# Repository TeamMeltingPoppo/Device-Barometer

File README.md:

# Device-Template

> A template for building applications for Twelite

This project is developed and maintained by the Team NABA

## Dependencies

To build embedded programs using this template you'll need:

- KiCad Version: 8.0.0, or a newer version.

- Git client

- Github CLI (optional)

## Usage

1. Repositoryを作成するときに、Repository Templateとして`TeamMeltingPoppo/Device-Template`を選択してください。

2. Repository名は、`Device-`から始まる名前にしてください。

3. 作成したRepositoryに移動し、`setup.sh`を実行してください。

```sh
sh ./setup.sh
```

これで、プロジェクトの初期設定が完了しました。

## Using this template with GitHub CLI

```sh
gh repo create ${repo name} --template https://github.com/BirdmanTeamNaba/Device-Template -c
cd ${repo name}
sh ./setup.sh
```

注. 自分のアカウントにRepositoryが作られます。

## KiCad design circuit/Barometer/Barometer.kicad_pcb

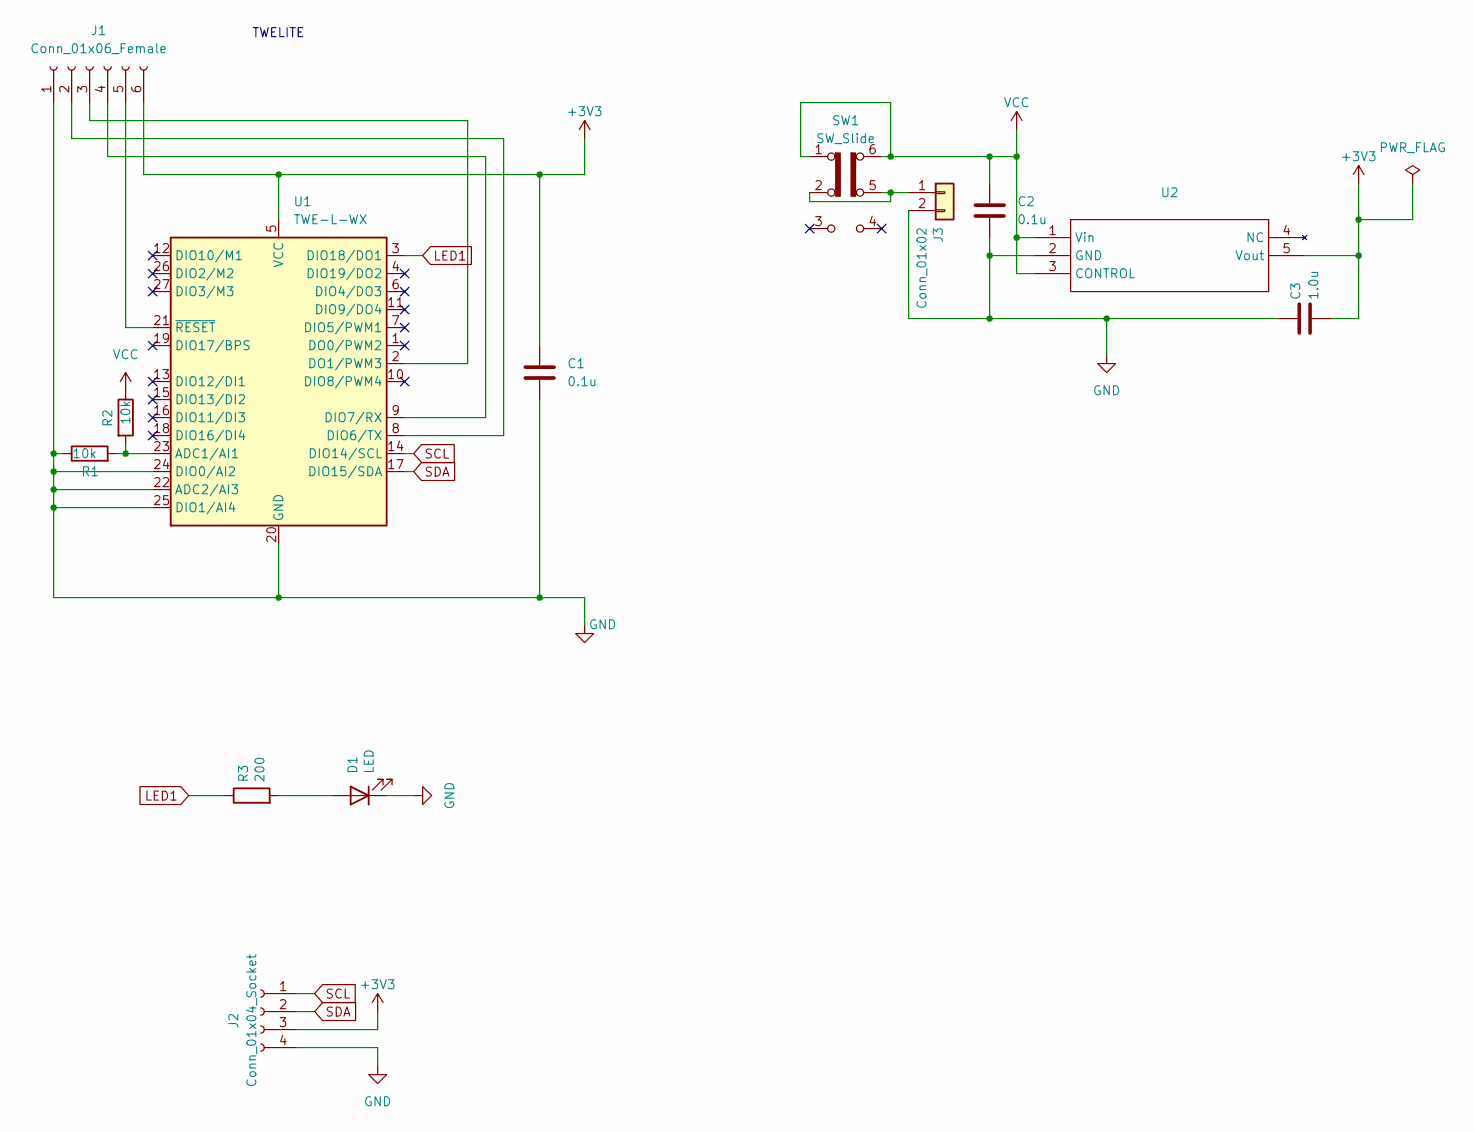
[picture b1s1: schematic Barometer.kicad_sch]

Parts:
C1, C2: 0.1u; C_0603_1608Metric_Pad1.08x0.95mm_HandSolder
C3: 1.0u; C_0603_1608Metric_Pad1.08x0.95mm_HandSolder
D1: LED; D_0603_1608Metric_Pad1.05x0.95mm_HandSolder
J1: Conn_01x06_Female; PinSocket_1x06_P2.54mm_Vertical
J2: Conn_01x04_Socket; NS-Tech_Grove_1x04_P2mm_Vertical
J3: Conn_01x02; JST_PH_B2B-PH-K_1x02_P2.00mm_Vertical
R1, R2: 10k; R_0603_1608Metric_Pad0.98x0.95mm_HandSolder
R3: 200; R_0603_1608Metric_Pad0.98x0.95mm_HandSolder
SW1: SW_Slide
U1: TWE-L-WX; MonoWireless_TWE-L-WX
U2: SOT95P280X130-5N

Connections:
+3V3: C1.1, C3.2, J1.6, J2.3, U1.5 (VCC), U2.5 (Vout)
GND: C1.2, C2.2, C3.1, D1.1 (K), J1.1, J2.4, J3.2, R1.1, U1.20 (GND), U1.22 (ADC2/AI3), U1.24 (DIO0/AI2), U1.25 (DIO1/AI4), U1.28 (GND), U1.30 (GND), U1.31 (GND), U1.32 (GND), U2.2 (GND)
LED1: R3.1, U1.3 (DIO18/DO1)
unnamed: D1.2 (A), R3.2
unnamed: J1.2, U1.8 (DIO6/TX)
unnamed: J1.3, U1.2 (DO1/PWM3)
unnamed: J1.4, U1.9 (DIO7/RX)
unnamed: J1.5, U1.21 (~RESET)
unnamed: J3.1, SW1.2 (B), SW1.5 (B)
unnamed: R1.2, R2.2, U1.23 (ADC1/AI1)
SCL: J2.1, U1.14 (DIO14/SCL)
SDA: J2.2, U1.17 (DIO15/SDA)
VCC: C2.1, R2.1, SW1.1 (A), SW1.6 (C), U2.1 (Vin), U2.3 (CONTROL)

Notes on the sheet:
TWELITE

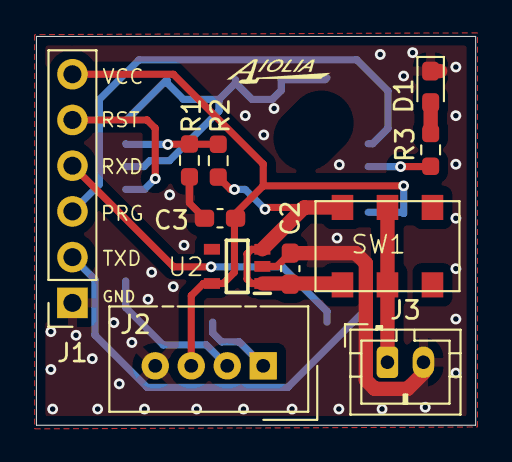
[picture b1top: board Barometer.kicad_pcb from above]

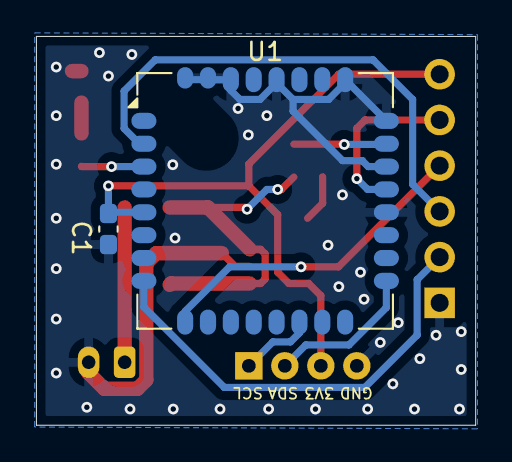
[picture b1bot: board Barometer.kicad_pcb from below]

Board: 2 copper layers, 24.4 x 21.6 mm, 13 parts (2 on the bottom side), 13 nets.

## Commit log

2024-09-30 回路図&PCBを追加
